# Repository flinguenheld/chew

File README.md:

A crunched 34 key choc-spaced keyboard.

&nbsp;

---

# Split

<div align="center">
  
</div>

The original.

### Requirements

- 2x PCB
- 2x MCU board [0xCB Gemini](https://github.com/0xCB-dev/0xCB-Gemini) or [RP2040-Zéro](https://www.waveshare.com/wiki/RP2040-Zero)
- 2x TRRS jack
- 34x switches Choc V1 **only**
- 34x keycaps Choc V1

Optional:
- 23x [Mill Max sockets](https://splitkb.com/collections/keyboard-parts/products/mill-max-low-profile-sockets)
- 34x [Kailh hotswap sockets](https://cdn.shopify.com/s/files/1/0588/1108/9090/files/5118-Choc-Socket.pdf?v=1686715063)
- 2x [Piezo buzzer](https://keeb.supply/products/piezo-buzzer)
- 2x Back PCB + screws and bolts
- 2x [Tenting pucks](https://splitkb.com/collections/keyboard-parts/products/tenting-puck)
- 2x [Tripods](https://www.manfrotto.com/us-en/pocket-support-large-black-mp3-bk/)

### Test

You can print these templates to test if it fits your hands:  
- [Left](./images/shape_left.pdf)
- [Right](./images/shape_right.pdf)

### Firmware

Chew is now running with it's [custom firmware](https://github.com/flinguenheld/rusty_chew) written in rust ! 🦀  

It also runs on [QMK](https://docs.qmk.fm/#/),  you can see it's [folder](https://github.com/qmk/qmk_firmware/tree/master/keyboards/chew/split) and my [keymap](https://github.com/flinguenheld/qmk_chew).

### How to build

Check the [wiki](https://github.com/flinguenheld/chew/wiki).

### Brainwave

Chew is a mix of these two cool keyboards:  

[Ferris sweep](https://github.com/davidphilipbarr/Sweep)  
[Wubbo](https://github.com/cacheworks/Wubbo)

&nbsp;

<div align="center" style="margin: 30px;">
  
</div>

---

# Mono

<div align="center">
  
</div>

The same, monobloc though !

### Requirements

- 1x PCB
- 1x MCU board [0xCB Gemini](https://github.com/0xCB-dev/0xCB-Gemini) or [RP2040-Zéro](https://www.waveshare.com/wiki/RP2040-Zero)
- 34x [1N4148W SMD diodes](https://splitkb.com/collections/keyboard-parts/products/smd-diodes)
- 34x switches Choc V1 **only**
- 34x keycaps Choc V1

Optional:
- 18x [Mill Max sockets](https://splitkb.com/collections/keyboard-parts/products/mill-max-low-profile-sockets)
- 34x [Kailh hotswap sockets](https://cdn.shopify.com/s/files/1/0588/1108/9090/files/5118-Choc-Socket.pdf?v=1686715063)  
- 1x [Piezo buzzer](https://keeb.supply/products/piezo-buzzer)
- 1x Back PCB + screws and bolts

### Test

You can print this [template](./images/shape_mono.pdf) to test if it fits your hands.

### Firmware

The [rusty firmware](https://github.com/flinguenheld/rusty_chew) also works with this version. 🦀  

Or its [QMK folder](https://github.com/qmk/qmk_firmware/tree/master/keyboards/chew/mono) with my [keymap](https://github.com/flinguenheld/qmk_chew).  

### How to build

Check the [wiki](https://github.com/flinguenheld/chew/wiki).

&nbsp;

<div align="center" style="margin: 30px;">
  
</div>

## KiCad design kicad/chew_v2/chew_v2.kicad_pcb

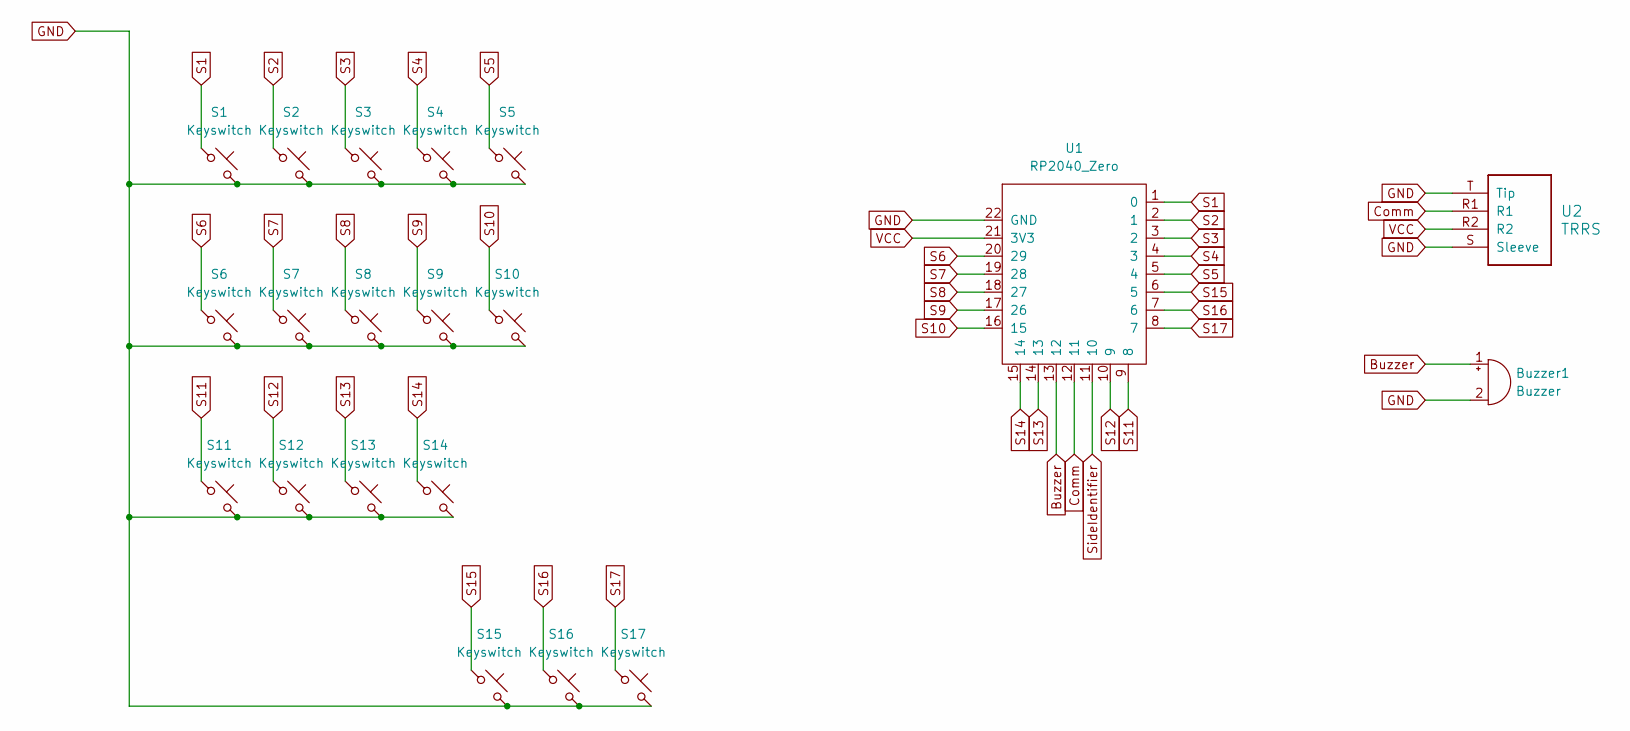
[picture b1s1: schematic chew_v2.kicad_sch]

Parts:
Buzzer1: Buzzer; Buzzer_Mallory_AST1109MLTRQ
S1, S3, S5, S7, S8, S9, S11, S12, S14, S16, S17: Keyswitch; Choc_V1_chew_reversible_1
S2, S4, S6, S10, S13, S15: Keyswitch; Choc_V1_chew_reversible_2
U1: RP2040_Zero; RP2040_Zero_chew_reversible
U2: TRRS; TRRS_chew_reversible

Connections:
Buzzer: Buzzer1.1 (+), U1.13 (12)
Comm: U1.12 (11), U2.R1
GND: Buzzer1.2 (-), S1.2, S2.2, S3.2, S4.2, S5.2, S6.2, S7.2, S8.2, S9.2, S10.2, S11.2, S12.2, S13.2, S14.2, S15.2, S16.2, S17.2, U1.22 (GND), U2.S (Sleeve), U2.T (Tip)
S1: S1.1, U1.1 (0)
S2: S2.1, U1.2 (1)
S3: S3.1, U1.3 (2)
S4: S4.1, U1.4 (3)
S5: S5.1, U1.5 (4)
S6: S6.1, U1.20 (29)
S7: S7.1, U1.19 (28)
S8: S8.1, U1.18 (27)
S9: S9.1, U1.17 (26)
S10: S10.1, U1.16 (15)
S11: S11.1, U1.9 (8)
S12: S12.1, U1.10 (9)
S13: S13.1, U1.14 (13)
S14: S14.1, U1.15 (14)
S15: S15.1, U1.6 (5)
S16: S16.1, U1.7 (6)
S17: S17.1, U1.8 (7)
SideIdentifier: U1.11 (10)
VCC: U1.21 (3V3), U2.R2

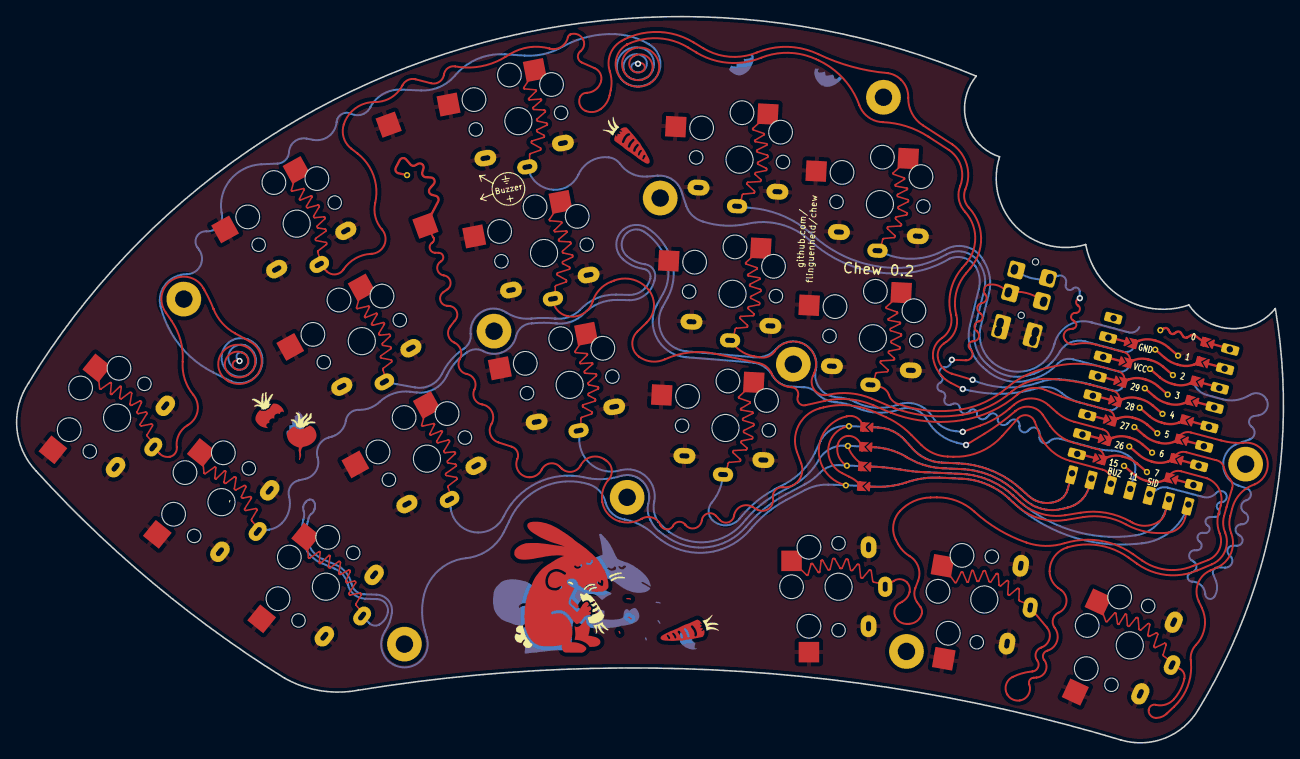
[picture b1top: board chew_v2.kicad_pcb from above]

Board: 2 copper layers, 160.3 x 91.9 mm, 20 parts (0 on the bottom side), 21 nets.

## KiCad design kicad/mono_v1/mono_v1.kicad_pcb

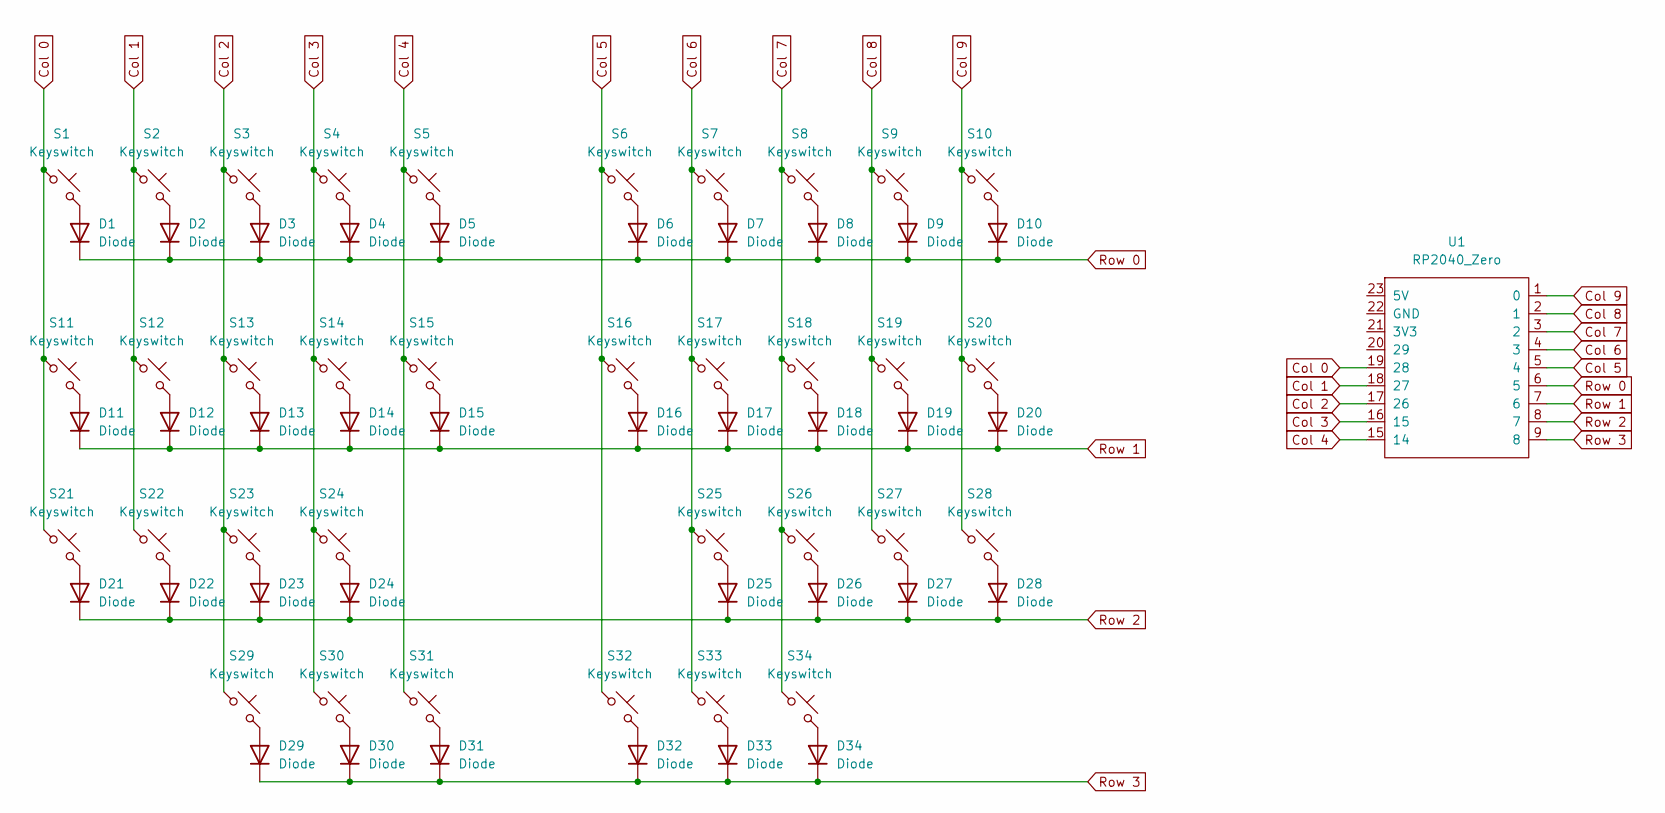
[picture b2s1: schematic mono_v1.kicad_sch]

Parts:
D1, D2, D3, D4, D5, D6, D7, D8, D9, D10, D11, D12, D13, D14, D15, D16, D17, D18, D19, D20, D21, D22, D23, D24, D25, D26, D27, D28, D29, D30, D31, D32, D33, D34: Diode; Diode_SOD-123_chew
S1, S2, S3, S4, S5, S6, S7, S8, S9, S10, S11, S12, S13, S14, S15, S16, S17, S18, S19, S20, S21, S22, S23, S24, S25, S26, S27, S28, S29, S30, S31, S32, S33, S34: Keyswitch; Choc_V1_chew
U1: RP2040_Zero; RP2040_Zero_chew_mono

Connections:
Col 0: S1.1, S11.1, S21.1, U1.19 (28)
Col 1: S2.1, S12.1, S22.1, U1.18 (27)
Col 2: S3.1, S13.1, S23.1, S29.1, U1.17 (26)
Col 3: S4.1, S14.1, S24.1, S30.1, U1.16 (15)
Col 4: S5.1, S15.1, S31.1, U1.15 (14)
Col 5: S6.1, S16.1, S32.1, U1.5 (4)
Col 6: S7.1, S17.1, S25.1, S33.1, U1.4 (3)
Col 7: S8.1, S18.1, S26.1, S34.1, U1.3 (2)
Col 8: S9.1, S19.1, S27.1, U1.2 (1)
Col 9: S10.1, S20.1, S28.1, U1.1 (0)
unnamed: D1.2 (A), S1.2
unnamed: D2.2 (A), S2.2
unnamed: D3.2 (A), S3.2
unnamed: D4.2 (A), S4.2
unnamed: D5.2 (A), S5.2
unnamed: D6.2 (A), S6.2
unnamed: D7.2 (A), S7.2
unnamed: D8.2 (A), S8.2
unnamed: D9.2 (A), S9.2
unnamed: D10.2 (A), S10.2
unnamed: D11.2 (A), S11.2
unnamed: D12.2 (A), S12.2
unnamed: D13.2 (A), S13.2
unnamed: D14.2 (A), S14.2
unnamed: D15.2 (A), S15.2
unnamed: D16.2 (A), S16.2
unnamed: D17.2 (A), S17.2
unnamed: D18.2 (A), S18.2
unnamed: D19.2 (A), S19.2
unnamed: D20.2 (A), S20.2
unnamed: D21.2 (A), S21.2
unnamed: D22.2 (A), S22.2
unnamed: D23.2 (A), S23.2
unnamed: D24.2 (A), S24.2
unnamed: D25.2 (A), S25.2
unnamed: D26.2 (A), S26.2
unnamed: D27.2 (A), S27.2
unnamed: D28.2 (A), S28.2
unnamed: D29.2 (A), S29.2
unnamed: D30.2 (A), S30.2
unnamed: D31.2 (A), S31.2
unnamed: D32.2 (A), S32.2
unnamed: D33.2 (A), S33.2
unnamed: D34.2 (A), S34.2
Row 0: D1.1 (K), D2.1 (K), D3.1 (K), D4.1 (K), D5.1 (K), D6.1 (K), D7.1 (K), D8.1 (K), D9.1 (K), D10.1 (K), U1.6 (5)
Row 1: D11.1 (K), D12.1 (K), D13.1 (K), D14.1 (K), D15.1 (K), D16.1 (K), D17.1 (K), D18.1 (K), D19.1 (K), D20.1 (K), U1.7 (6)
Row 2: D21.1 (K), D22.1 (K), D23.1 (K), D24.1 (K), D25.1 (K), D26.1 (K), D27.1 (K), D28.1 (K), U1.8 (7)
Row 3: D29.1 (K), D30.1 (K), D31.1 (K), D32.1 (K), D33.1 (K), D34.1 (K), U1.9 (8)

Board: 2 copper layers, 69 parts (0 on the bottom side), 48 nets, no tracks yet.

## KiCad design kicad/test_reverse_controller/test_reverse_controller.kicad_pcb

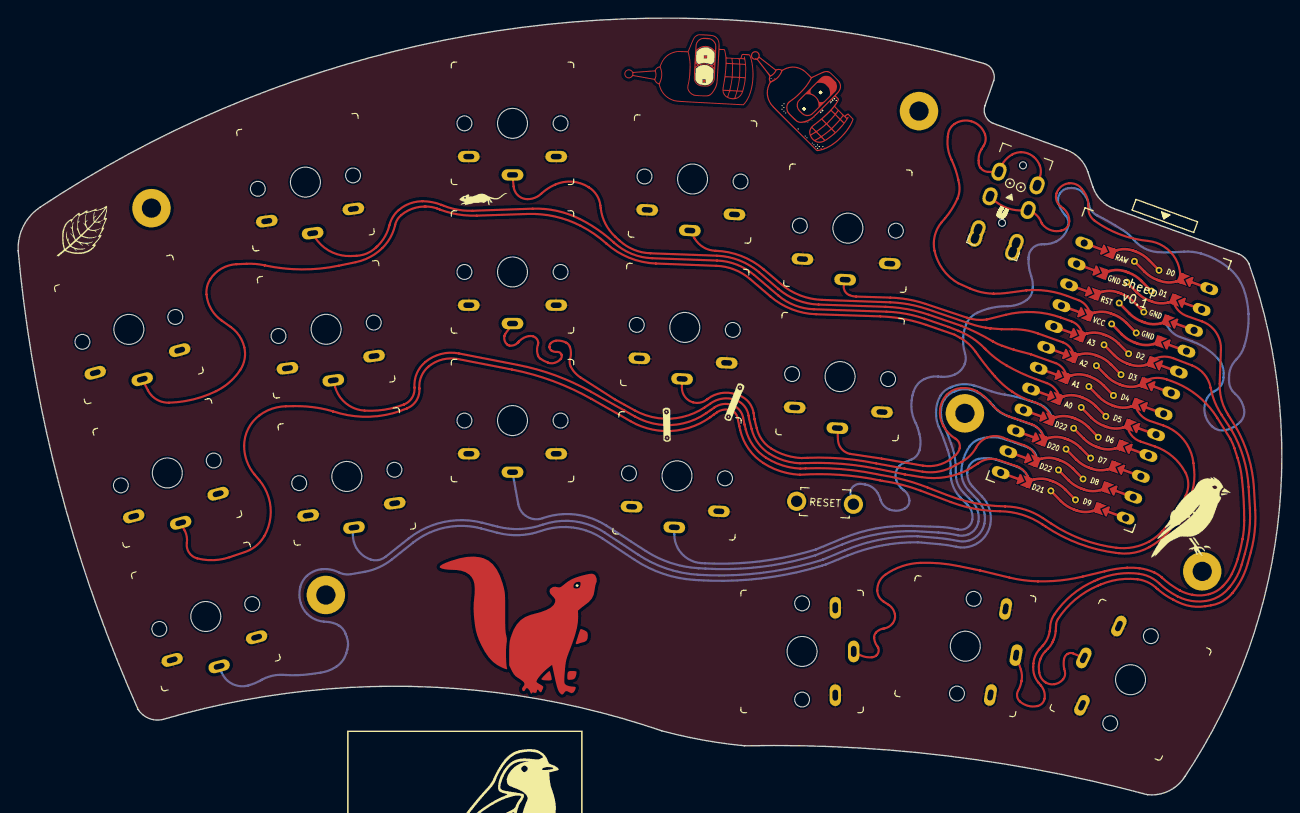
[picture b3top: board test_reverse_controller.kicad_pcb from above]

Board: 2 copper layers, 144.6 x 88.9 mm, 20 parts (0 on the bottom side), 21 nets.

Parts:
J2: AudioJack4dpb; TRRS-PJ-DPB2
RSW2: SW_PUSH; ResetSW_1side
SW1, SW2, SW3, SW4, SW5, SW6, SW7, SW8, SW9, SW10, SW11, SW12, SW13, SW14, SW15, SW16, SW17: SW_Push; SW_PG1350_rev_DPB
U1: ProMicro-kbd; ProMicro_jumpers_facedown

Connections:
Switch1: SW1.1, U1.20
Switch2: SW2.1, U1.19
Switch3: SW3.1, U1.18
Switch4: SW4.1, U1.17
Switch5: SW5.1, U1.16
Switch6: SW6.1, U1.15
Switch7: SW7.1, U1.14
Switch8: SW8.1, U1.13
Switch9: SW9.1, U1.8
Switch10: SW10.1, U1.7
Switch11: SW11.1, U1.9
Switch12: SW12.1, U1.10
Switch13: SW13.1, U1.11
Switch14: SW14.1, U1.12
Switch15: SW15.1, U1.2
Switch16: SW16.1, U1.5
Switch17: SW17.1, U1.6
Switch18: J2.R1, U1.1
gnd: J2.S, J2.T, RSW2.2, SW1.2, SW2.2, SW3.2, SW4.2, SW5.2, SW6.2, SW7.2, SW8.2, SW9.2, SW10.2, SW11.2, SW12.2, SW13.2, SW14.2, SW15.2, SW16.2, SW17.2, U1.3, U1.4, U1.23
reset: RSW2.1, U1.22
vcc: J2.R2, U1.21

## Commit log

2024-03-04 Init & place switchs
2024-03-05 Shape ok
2024-03-05 Set map
2024-03-05 Routes ok
2024-03-06 More curves
2024-03-09 Add qmk files
2024-03-10 Test reversed controller
2024-03-11 Reversed controller ok + up matrix pins
2024-03-12 Reverse pads & up mergins
2024-03-15 Add art
2024-03-15 Rename to chew
2024-03-15 Move that rabbit
2024-03-16 Add tenting puck
2024-03-18 Add backplate & art
2024-03-19 Ordered
2024-03-27 Up qmk info
2024-03-28 Enlarge pads
2024-03-29 Up backplate + add tenting hole version
2024-04-02 Add hotswap option
2024-04-03 Up column angles + edges
2024-04-04 Up backplates
2024-04-15 Add RP2040 zero
2024-04-16 Add routes
2024-04-17 Add backplate
2024-04-21 Rename to chew zero
2024-04-27 Add images
2024-04-30 QMK PR ok 🚀
2024-04-30 Add VBus
2024-05-01 Set VBus by default
2024-05-01 Up silkscreen
2024-05-10 Create mono schematics
2024-05-12 Add mono traces
2024-05-13 Mono tracks ok
2024-05-13 Create libs
2024-05-13 Replace footprints
2024-05-13 Mono shape ok
2024-05-20 Mono prod
2024-05-22 Simplify switch traces
2024-05-25 Up photos
2024-05-31 Mono release
2024-05-31 Crunched
2024-10-05 Treasure !
2025-02-18 Add rusty link & images
2025-02-20 Add rusty backplate
2025-03-06 Rusty readme
2025-04-25 Add buzzer & clean silkscreen
2025-05-13 Up readme v2
2025-05-29 Readme - Fix QMK link
2025-05-29 Readme - Up split QMK link
2025-09-05 Up backplates with buzzer holes
